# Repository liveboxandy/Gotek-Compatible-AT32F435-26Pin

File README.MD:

Initial schematic and gerbers for a Gotek compatible with an Artery AT32F435RGT7 chip and a 26 Pin FFC connector.

Used SFRKC30.AT4.35 PCB for most of the schematic and layout but used SFRC2D.B PCB for the 26 Pin FFC connections.

Used photographs and a multimeter along with removing U1 and U3 on the SFRKC30.AT4.35 to get to the traces underneath.

Where possible I followed the original PCB routing of the SFRKC30.AT4.35 but Kicad has some different rules for trace widths (between pins 5&6 of U8, which isn't fitted for FlashFloppy).

Included all non pops so that the ibom displays everything.

U8 is not fitted for use with FlashFloppy.]

LEDs 3 and 5 are not normally fitted.

Added ibom (bom/ibom.html).

Restructured folders

Works as a replacement for the floppy in a TDS3052 Oscilloscope. Just needs a very slim case (13mm)

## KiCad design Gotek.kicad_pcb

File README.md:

Initial schematic and gerbers for a Gotek compatible with an Artery AT32F435RGT7 chip and a 26 Pin FFC connector.

Used SFRKC30.AT4.35 PCB for most of the schematic and layout but used SFRC2D.B PCB for the 26 Pin FFC connections.

Used photographs and a multimeter along with removing U1 and U3 on the SFRKC30.AT4.35 to get to the traces underneath.

Where possible I followed the original PCB routing of the SFRKC30.AT4.35 but Kicad has some different rules for trace widths (between pins 5&6 of U8, which isn't fitted for FlashFloppy).

Included all non pops so that the ibom displays everything.

U8 is not fitted for use with FlashFloppy.]

LEDs 3 and 5 are not normally fitted.

Added ibom (bom/ibom.html).

Restructured folders

Works as a replacement for the floppy in a TDS3052 Oscilloscope. Just needs a very slim case (13mm)

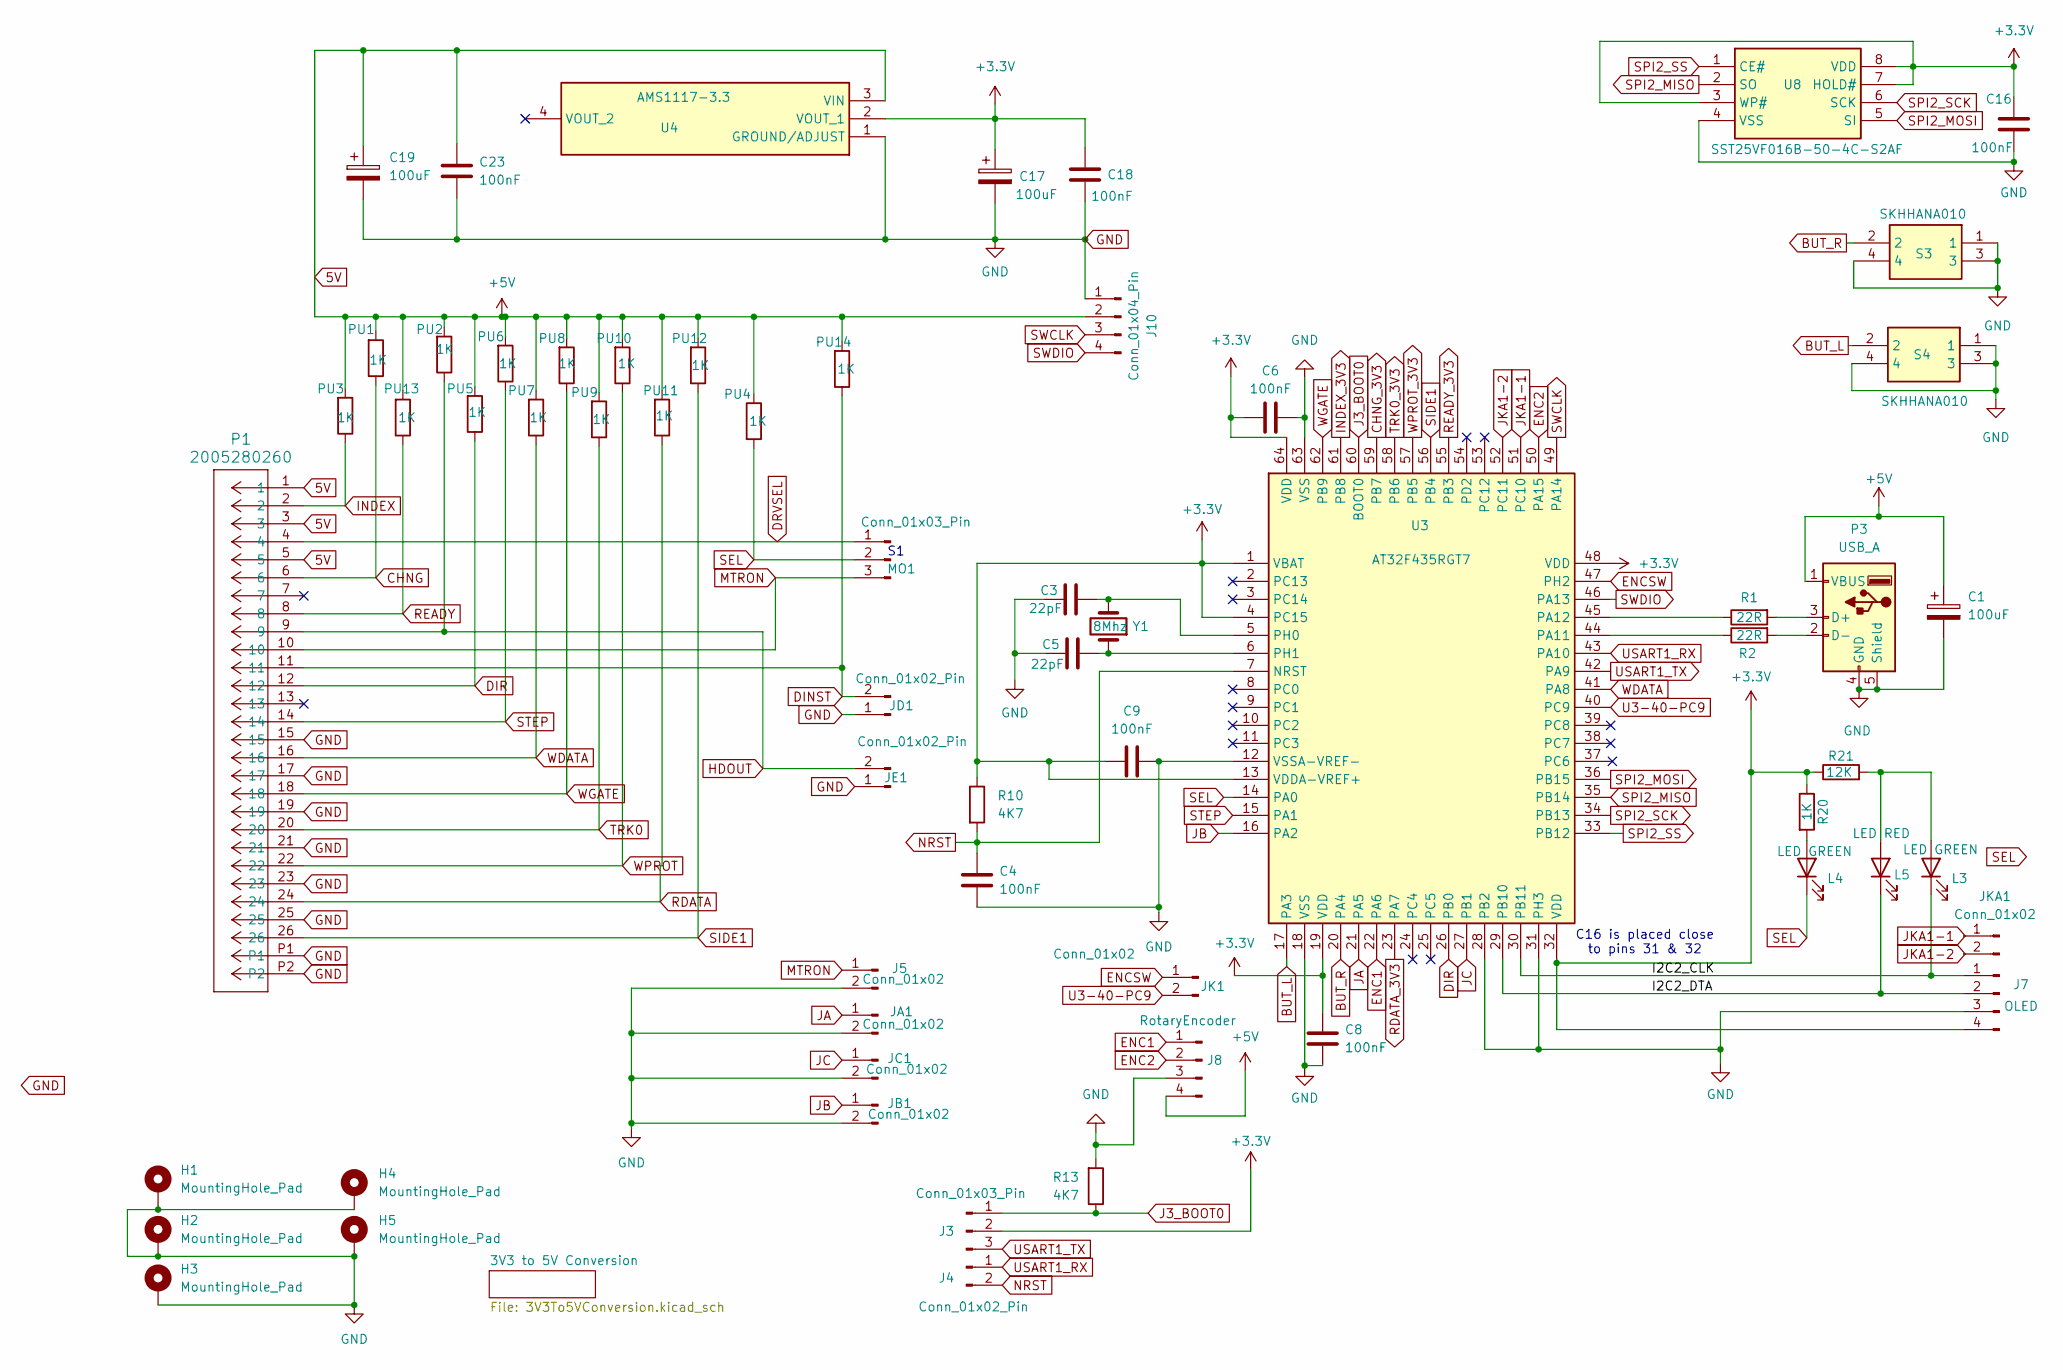
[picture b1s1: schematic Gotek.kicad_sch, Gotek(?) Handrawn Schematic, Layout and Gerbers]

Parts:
C1, C17, C19: 100uF; CP_Radial_D5.0mm_P2.50mm
C3, C5: 22pF; C_0805_2012Metric_Pad1.18x1.45mm_HandSolder
C4, C6, C8, C9, C16, C18, C23: 100nF; C_0805_2012Metric_Pad1.18x1.45mm_HandSolder
H1, H2, H3, H4, H5: MountingHole_Pad; MountingHole_M3_Pad
J3: Conn_01x03_Pin; PinHeader_1x03_P2.54mm_Vertical
J4: Conn_01x02_Pin; PinHeader_1x02_P2.54mm_Vertical
J5: Conn_01x02; PinHeader_1x02_P2.54mm_Vertical
J7: OLED; PinHeader_2x02_P2.54mm_Horizontal
J8: RotaryEncoder; PinHeader_2x02_P2.54mm_Horizontal
J10: Conn_01x04_Pin; PinHeader_1x04_P2.54mm_Vertical
JA1: Conn_01x02; PinHeader_1x02_P2.54mm_Vertical
JB1: Conn_01x02; PinHeader_1x02_P2.54mm_Vertical
JC1: Conn_01x02; PinHeader_1x02_P2.54mm_Vertical
JD1: Conn_01x02_Pin; PinHeader_1x02_P2.54mm_Horizontal
JE1: Conn_01x02_Pin; PinHeader_1x02_P2.54mm_Horizontal
JK1: Conn_01x02; PinHeader_2x01_P2.54mm_Horizontal
JKA1: Conn_01x02; PinHeader_2x01_P2.54mm_Horizontal
L3, L4: LED GREEN; LED_D4.0mm
L5: LED RED; LED_D4.0mm
MO1: Conn_01x03_Pin; PinHeader_1x03_P2.54mm_Horizontal
P1: 2005280260; MOLEX_CON_2005280260
P3: USB_A; USB_A_Molex_67643_Horizontal
PU1, PU2, PU3, PU4, PU5, PU6, PU7, PU8, PU9, PU10, PU11, PU12, PU13, PU14: 1K; R_0805_2012Metric_Pad1.20x1.40mm_HandSolder
R1, R2: 22R; R_0805_2012Metric_Pad1.20x1.40mm_HandSolder
R10, R13: 4K7; R_0805_2012Metric_Pad1.20x1.40mm_HandSolder
R20: 1K; R_0805_2012Metric_Pad1.20x1.40mm_HandSolder
R21: 12K; R_0805_2012Metric_Pad1.20x1.40mm_HandSolder
S3, S4: SKHHANA010; SKHHLQA010; Mouser Part Number 688-SKHHAN
U3: AT32F435RGT7; QFP50P1200X1200X160-64N; Manufacturer_Part_Number AT32F435RGT7
U4: AMS1117-3.3; SOT229P700X180-4N; Manufacturer_Part_Number ams1117-3.3v
U8: SST25VF016B-50-4C-S2AF; SOIC127P790X216-8N; Mouser Part Number 579-25VF016B504CS2AF
Y1: 8Mhz; Crystal_HC18-U_Vertical

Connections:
5V: C1.1, C19.1, C23.1, J8.4, J10.2, P1.1, P1.3, P1.5, P3.1 (VBUS), PU1.2, PU2.2, PU3.2, PU4.1, PU5.2, PU6.2, PU7.2, PU8.2, PU9.2, PU10.2, PU11.2, PU12.2, PU13.2, PU14.2, U4.3 (VIN); also elsewhere on the board
+3.3V: C6.1, C8.1, C9.2, C16.2, C17.1, C18.2, J3.2, J7.4, R10.1, R20.1, R21.1, U3.1 (VBAT), U3.4 (PC15), U3.13 (VDDA-VREF+), U3.19 (VDD), U3.32 (VDD), U3.48 (VDD), U3.64 (VDD), U4.2 (VOUT_1), U8.3 (WP#), U8.7 (HOLD#), U8.8 (VDD)
/I2C2_CLK: J7.1, L3.1 (K), U3.30 (PB11)
/I2C2_DTA: J7.2, L5.1 (K), U3.29 (PB10)
BUT_L: S4.2, U3.17 (PA3)
BUT_R: S3.2, U3.20 (PA4)
CHNG: P1.6, PU1.1; also elsewhere on the board
CHNG_3V3: U3.59 (PB7); also elsewhere on the board
DINST: JD1.2, P1.11, PU14.1
DIR: P1.12, PU5.1, U3.26 (PB0)
DRVSEL: MO1.1, P1.4
ENC1: J8.1, U3.22 (PA6)
ENC2: J8.2, U3.50 (PA15)
ENCSW: JK1.1, U3.47 (PH2)
GND: C1.2, C3.1, C4.2, C5.2, C6.2, C8.2, C9.1, C16.1, C17.2, C18.1, C19.2, C23.2, H1.1, H2.1, H3.1, H4.1, H5.1, J5.2, J7.3, J8.3, J10.1, JA1.2, JB1.2, JC1.2, JD1.1, JE1.1, P1.15, P1.17, P1.19, P1.21, P1.23, P1.25, P1.P1, P1.P2, P3.4 (GND), P3.5 (Shield), R13.2, S3.1, S3.3, S3.4, S4.1, S4.3, S4.4, U3.12 (VSSA-VREF-), U3.18 (VSS), U3.28 (PB2), U3.31 (PH3), U3.63 (VSS), U4.1 (GROUND/ADJUST), U8.4 (VSS); also elsewhere on the board
HDOUT: JE1.2, P1.9, PU2.1
INDEX: P1.2, PU3.1; also elsewhere on the board
INDEX_3V3: U3.61 (PB8); also elsewhere on the board
J3_BOOT0: J3.1, R13.1, U3.60 (BOOT0)
JA: JA1.1, U3.21 (PA5)
JB: JB1.1, U3.16 (PA2)
JC: JC1.1, U3.27 (PB1)
JKA1-1: JKA1.1, U3.51 (PC10)
JKA1-2: JKA1.2, U3.52 (PC11)
MTRON: J5.1, MO1.3, P1.10
NRST: C4.1, J4.2, R10.2, U3.7 (NRST)
unnamed: L3.2 (A), L5.2 (A), R21.2
unnamed: L4.2 (A), R20.2
unnamed: P3.3 (D+), R1.2
unnamed: P3.2 (D-), R2.2
unnamed: R2.1, U3.44 (PA11)
unnamed: R1.1, U3.45 (PA12)
unnamed: C3.2, U3.5 (PH0), Y1.2
unnamed: C5.1, U3.6 (PH1), Y1.1
RDATA: P1.24, PU11.1; also elsewhere on the board
RDATA_3V3: U3.23 (PA7); also elsewhere on the board
READY: P1.8, PU13.1; also elsewhere on the board
READY_3V3: U3.55 (PB3); also elsewhere on the board
SEL: L4.1 (K), MO1.2, PU4.2, U3.14 (PA0)
SIDE1: P1.26, PU12.1, U3.56 (PB4)
SPI2_MISO: U3.35 (PB14), U8.2 (SO)
SPI2_MOSI: U3.36 (PB15), U8.5 (SI)
SPI2_SCK: U3.34 (PB13), U8.6 (SCK)
SPI2_SS: U3.33 (PB12), U8.1 (CE#)
STEP: P1.14, PU6.1, U3.15 (PA1)
SWCLK: J10.3, U3.49 (PA14)
SWDIO: J10.4, U3.46 (PA13)
TRK0: P1.20, PU9.1; also elsewhere on the board
TRK0_3V3: U3.58 (PB6); also elsewhere on the board
U3-40-PC9: JK1.2, U3.40 (PC9)
USART1_RX: J4.1, U3.43 (PA10)
USART1_TX: J3.3, U3.42 (PA9)
WDATA: P1.16, PU7.1, U3.41 (PA8)
WGATE: P1.18, PU8.1, U3.62 (PB9)
WPROT: P1.22, PU10.1; also elsewhere on the board
WPROT_3V3: U3.57 (PB5); also elsewhere on the board

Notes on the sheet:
C16 is placed close to pins 31 & 32

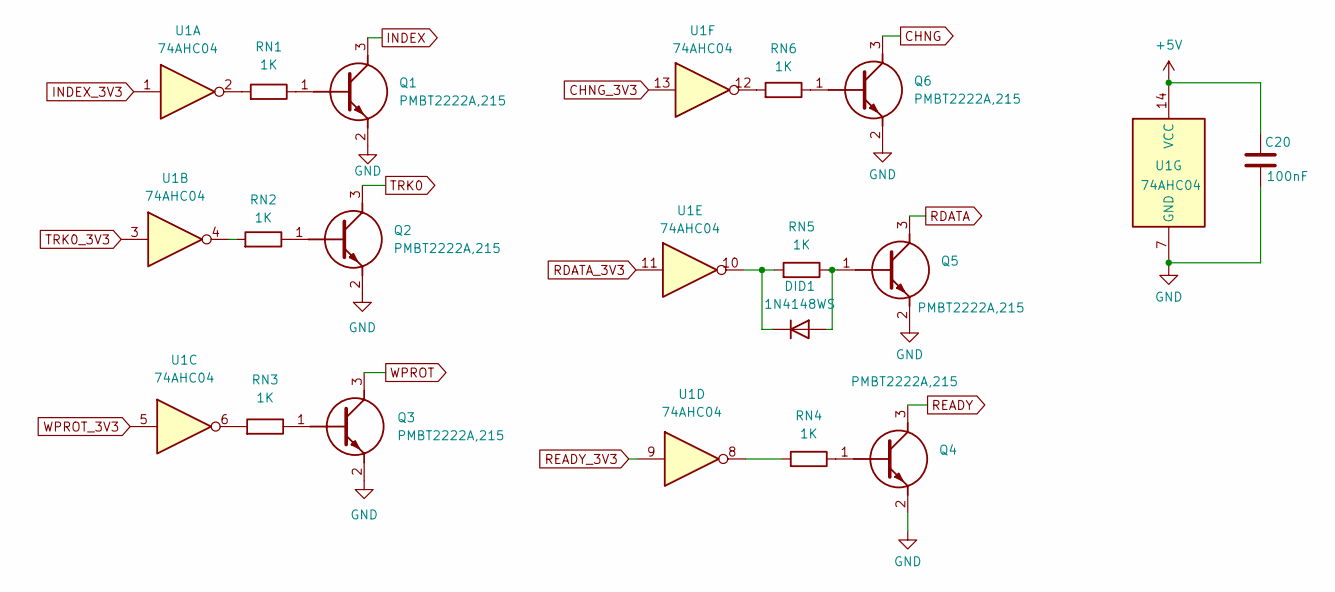
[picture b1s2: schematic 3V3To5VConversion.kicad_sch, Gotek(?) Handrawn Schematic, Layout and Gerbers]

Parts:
C20: 100nF; C_0805_2012Metric_Pad1.18x1.45mm_HandSolder
DID1: 1N4148WS; SODFL2512X90N
Q1, Q2, Q3, Q4, Q5, Q6: PMBT2222A,215; SOT95P280X130-3N; Mouser Part Number 771-PMBT2222A-T/R
RN1, RN2, RN3, RN4, RN5, RN6: 1K; R_0805_2012Metric_Pad1.20x1.40mm_HandSolder
U1: 74AHC04; SO-14_3.9x8.65mm_P1.27mm

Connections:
5V: C20.2, U1.14 (VCC); also elsewhere on the board
CHNG: Q6.3 (C); also elsewhere on the board
CHNG_3V3: U1.13; also elsewhere on the board
GND: C20.1, Q1.2 (E), Q2.2 (E), Q3.2 (E), Q4.2 (E), Q5.2 (E), Q6.2 (E), U1.7 (GND); also elsewhere on the board
INDEX: Q1.3 (C); also elsewhere on the board
INDEX_3V3: U1.1; also elsewhere on the board
unnamed: DID1.2 (A), Q5.1 (B), RN5.1
unnamed: DID1.1 (K), RN5.2, U1.10
unnamed: Q1.1 (B), RN1.1
unnamed: Q2.1 (B), RN2.1
unnamed: Q3.1 (B), RN3.1
unnamed: Q4.1 (B), RN4.1
unnamed: Q6.1 (B), RN6.1
unnamed: RN1.2, U1.2
unnamed: RN2.2, U1.4
unnamed: RN3.2, U1.6
unnamed: RN4.2, U1.8
unnamed: RN6.2, U1.12
RDATA: Q5.3 (C); also elsewhere on the board
RDATA_3V3: U1.11; also elsewhere on the board
READY: Q4.3 (C); also elsewhere on the board
READY_3V3: U1.9; also elsewhere on the board
TRK0: Q2.3 (C); also elsewhere on the board
TRK0_3V3: U1.3; also elsewhere on the board
WPROT: Q3.3 (C); also elsewhere on the board
WPROT_3V3: U1.5; also elsewhere on the board

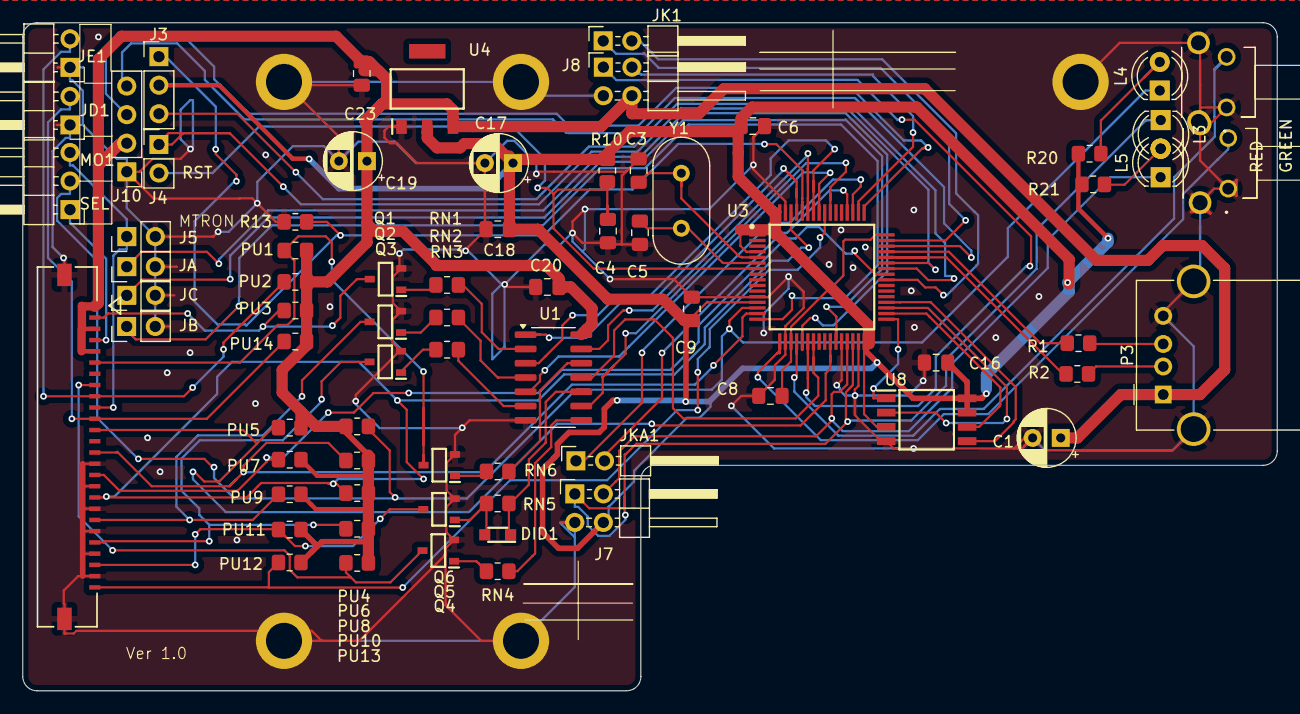
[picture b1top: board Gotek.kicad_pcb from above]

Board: 2 copper layers, 111.6 x 59.4 mm, 77 parts (0 on the bottom side), 68 nets.

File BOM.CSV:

"Reference","Value","Datasheet","Footprint","Qty","DNP"
"C1,C17,C19","100uF","~","Capacitor_THT:CP_Radial_D5.0mm_P2.50mm","3",""
"C3,C5","22pF","~","Capacitor_SMD:C_0805_2012Metric_Pad1.18x1.45mm_HandSolder","2",""
"C4,C6,C8,C9,C16,C18,C20,C23","100nF","~","Capacitor_SMD:C_0805_2012Metric_Pad1.18x1.45mm_HandSolder","8",""
"DID1","1N4148WS","https://www.vishay.com/docs/85751/1n4148ws.pdf","Gotek:SODFL2512X90N","1",""
"J3,MO1","Conn_01x03_Pin","~","Connector_PinHeader_2.54mm:PinHeader_1x03_P2.54mm_Horizontal,Connector_PinHeader_2.54mm:PinHeader_1x03_P2.54mm_Vertical","2",""
"J4,JD1,JE1","Conn_01x02_Pin","~","Connector_PinHeader_2.54mm:PinHeader_1x02_P2.54mm_Horizontal,Connector_PinHeader_2.54mm:PinHeader_1x02_P2.54mm_Vertical","3",""
"J5,JA1,JB1,JC1,JK1,JKA1","Conn_01x02","~","Connector_PinHeader_2.54mm:PinHeader_1x02_P2.54mm_Vertical,Connector_PinHeader_2.54mm:PinHeader_2x01_P2.54mm_Horizontal","6",""
"J7","OLED","~","Connector_PinHeader_2.54mm:PinHeader_2x02_P2.54mm_Horizontal","1",""
"J8","RotaryEncoder","~","Connector_PinHeader_2.54mm:PinHeader_2x02_P2.54mm_Horizontal","1",""
"J10","Conn_01x04_Pin","~","Connector_PinHeader_2.54mm:PinHeader_1x04_P2.54mm_Vertical","1",""
"L3,L4","LED GREEN","~","LED_THT:LED_D4.0mm","2",""
"L5","LED RED","~","LED_THT:LED_D4.0mm","1",""
"P1","2005280260","2005280260","Gotek:MOLEX_CON_2005280260","1",""
"P3","USB_A","~","Connector_USB:USB_A_Molex_67643_Horizontal","1",""
"PU1,PU2,PU3,PU4,PU5,PU6,PU7,PU8,PU9,PU10,PU11,PU12,PU13,PU14,R20,RN1,RN2,RN3,RN4,RN5,RN6","1K","~","Resistor_SMD:R_0805_2012Metric_Pad1.20x1.40mm_HandSolder","21",""
"Q1,Q2,Q3,Q4,Q5,Q6","PMBT2222A,215","https://assets.nexperia.com/documents/data-sheet/PMBT2222A.pdf","Gotek:SOT95P280X130-3N","6",""
"R1,R2","22R","~","Resistor_SMD:R_0805_2012Metric_Pad1.20x1.40mm_HandSolder","2",""
"R10,R13","4K7","~","Resistor_SMD:R_0805_2012Metric_Pad1.20x1.40mm_HandSolder","2",""
"R21","12K","~","Resistor_SMD:R_0805_2012Metric_Pad1.20x1.40mm_HandSolder","1",""
"S3,S4","SKHHANA010","https://www.mouser.co.uk/datasheet/2/15/SKHH-1370651.pdf","Gotek:SKHHLQA010","2",""
"U1","74AHC04","https://assets.nexperia.com/documents/data-sheet/74AHC_AHCT04.pdf","Package_SO:SO-14_3.9x8.65mm_P1.27mm","1",""
"U3","AT32F435RGT7","","Gotek:QFP50P1200X1200X160-64N","1",""
"U4","AMS1117-3.3","http://www.advanced-monolithic.com/pdf/ds1117.pdf","Gotek:SOT229P700X180-4N","1",""
"U8","SST25VF016B-50-4C-S2AF","https://ww1.microchip.com/downloads/en/DeviceDoc/20005044C.pdf","Gotek:SOIC127P790X216-8N","1",""
"Y1","8Mhz","~","Crystal:Crystal_HC18-U_Vertical","1",""

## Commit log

2025-03-06 Add files via upload
    Initial Release, NOT BUILT YET
2025-03-06 Add files via upload
    Add License
2025-03-06 Create LICENSE file
2025-03-06 Remove old LICENSE.htm
2025-04-11 Add files via upload
    Removed L3 Green LED and changed R21 to 12K to reduce it's brightness. Also increased the pad sizes for the diode D1D to make it easier to hand solder. Minor changes to silk screen.
2025-10-23 Minor Changes
    Update for Kicad 9
    Added ibom (bom/ibom.html)
    Restructured folders.
2025-10-23 Update README to be more readable
